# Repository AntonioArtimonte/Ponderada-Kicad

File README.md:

# Placa Auxiliar para Raspberry Pi Pico W

Este repositório contém todos os arquivos e documentações relacionados ao desenvolvimento de uma placa de circuito impresso (PCB) projetada para se integrar com o Raspberry Pi Pico W. A placa foi desenvolvida como parte da atividade do módulo de CAD para placas eletrônicas.

## Visão Geral do Projeto

O projeto consiste em uma placa de circuito impresso que acomoda um Raspberry Pi Pico W através de um dispositivo conector. Além disso, a placa inclui:

- Uma interface de potência, composta por um relé e um transistor, para controlar dispositivos de alta potência com uma saída de dois pinos.
- Um led conectado através de um resistor de 10k a Raspberry Pi Pico
- Um dispositivo de entrada, neste caso, um sensor de temperatura analógico, para monitorar as condições ambientais ligado diretamente a placa Raspberry Pi Pico.

## Autor

Desenvolvido por Antonio Artimonte Vaz Guimarães

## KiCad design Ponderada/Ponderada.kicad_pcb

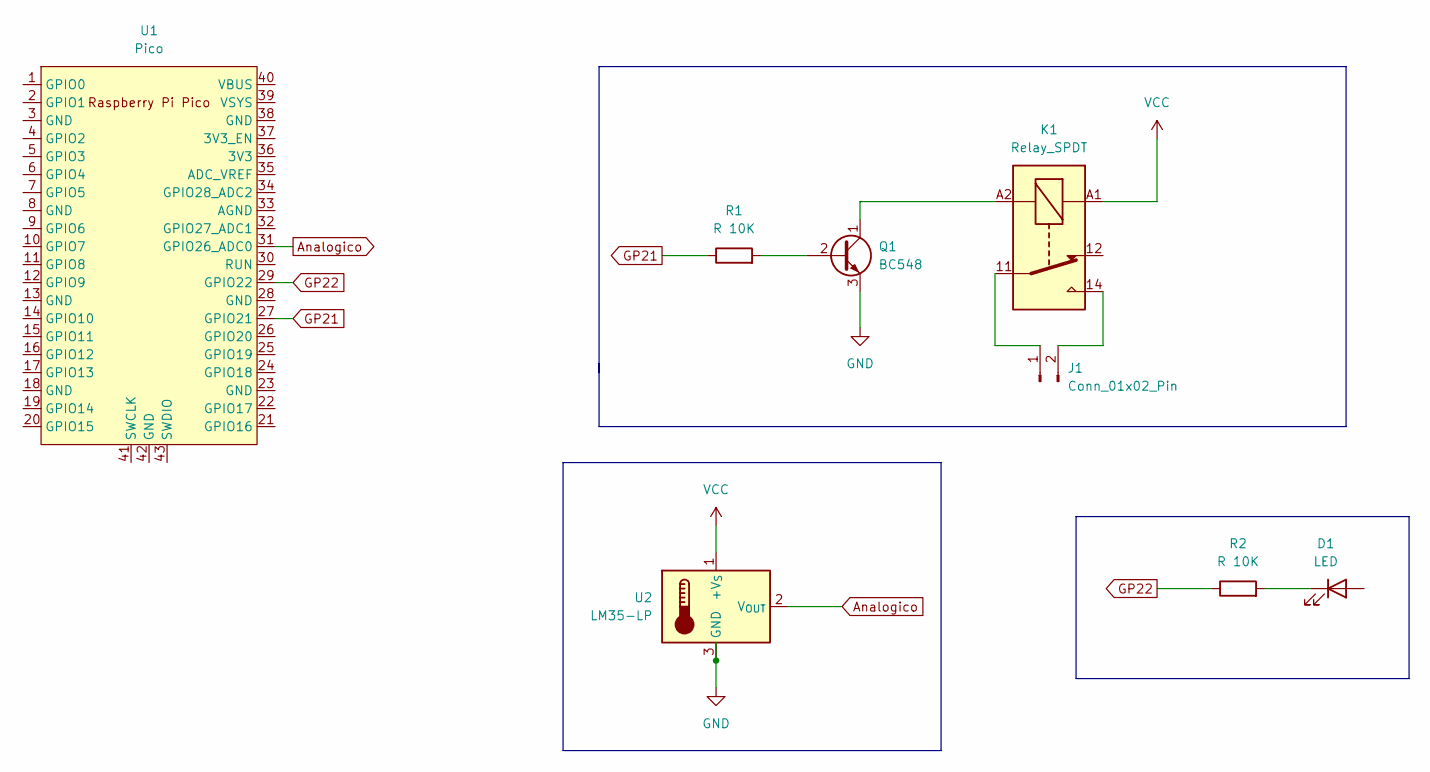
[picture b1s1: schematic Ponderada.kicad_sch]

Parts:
D1: LED; LED_D5.0mm_Clear
J1: Conn_01x02_Pin; JST_PH_S2B-PH-K_1x02_P2.00mm_Horizontal
K1: Relay_SPDT; Relay_1-Form-C_Schrack-RYII_RM3.2mm
Q1: BC548; TO-92_Inline
R1, R2: R 10K; R_Axial_DIN0414_L11.9mm_D4.5mm_P25.40mm_Horizontal
U1: Pico; RPi_Pico_SMD_TH
U2: LM35-LP; SOIC-8W_5.3x5.3mm_P1.27mm

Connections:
Analogico: U1.31 (GPIO26_ADC0), U2.2 (V_{OUT})
GND: D1.2 (A), Q1.3 (E), U2.3 (GND)
GP21: R1.1, U1.27 (GPIO21)
GP22: R2.1, U1.29 (GPIO22)
unnamed: D1.1 (K), R2.2
unnamed: J1.1, K1.11
unnamed: J1.2, K1.14
unnamed: Q1.2 (B), R1.2
unnamed: K1.A2, Q1.1 (C)
VCC: K1.A1, U2.1 (+V_{S})

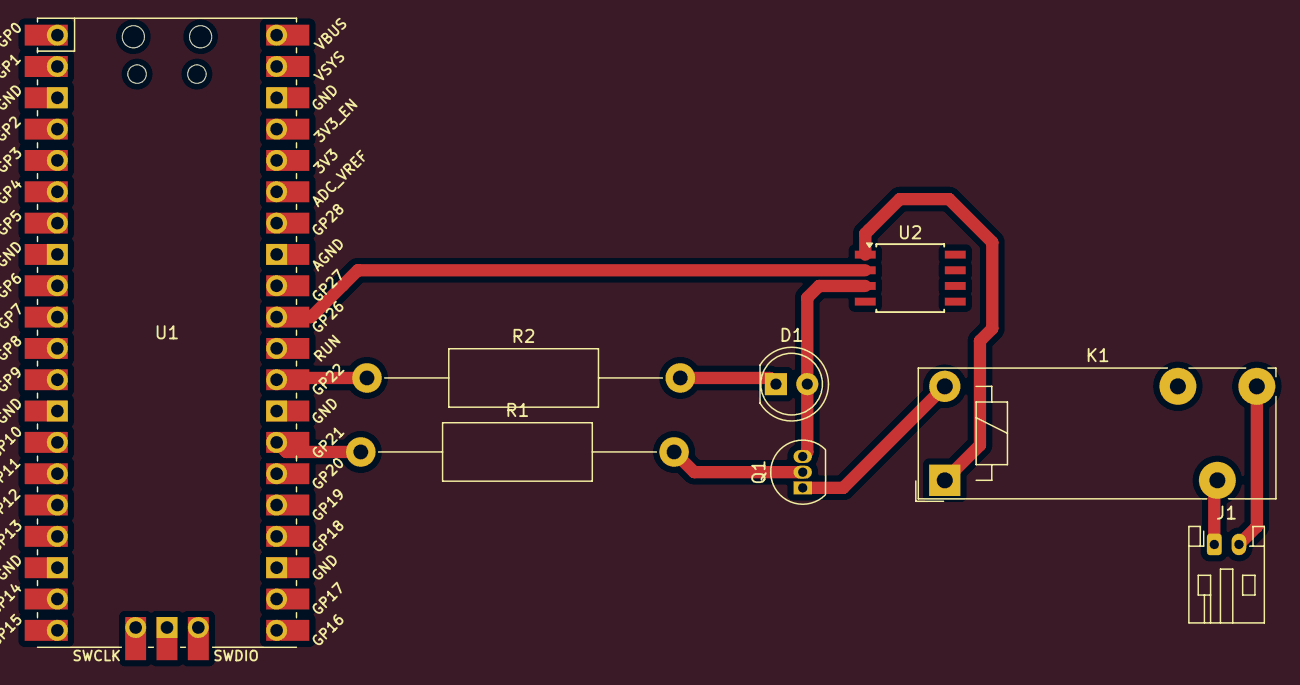
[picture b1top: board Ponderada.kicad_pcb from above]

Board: 2 copper layers, 8 parts (0 on the bottom side), 10 nets.

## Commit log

2024-03-28 commit inicial
